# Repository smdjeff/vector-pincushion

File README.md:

# vector-pincushion

## Allows CRT swaps between various vector game boards and deflection boards. 

Finding tubes for vector arcade displays is difficult and being able to mix and match deflection boards, TV CRTs and arcade PCBs is becoming a necessity. Some arcade games relied on an exact combination of tube shape, yoke, and game board to correctly display.  There may be analog corrections on either the arcade PCB or the deflection board or even the CRT yoke and neck. The Amplifone deflection boards contain no corrections, so when used with a Wells Gardner game PCB adding a correction board is a necessity to add the missing circuity. Tempest PCBs lacked the adjustments as did Sega vectors, but more advanced games like Major Havoc and Star Wars had them on the game boards rather than the deflection boards.

This board allows correction or decorrection as required depending on what you have combined.

### Linearity adjustment 
applies the function _X = X * k_ and _Y = Y * k_ allowing calibration of straightness in diagonally drawn vectors. When set to expansion mode, the correction will cause lines to be drawn further and further outward from the center. When set to shrink mode, the correction will cause lines to be drawn closer and closer the further they are from the center.

### Pincushion correction 
applies the function _X = X * k * Y_ and _Y = Y * k * X_ allowing for each axis to be drawn further or closer toward the center depending on the *opposite* axis distance from center.

## Features

* Barreling correction mode
* Pincushion correction mode
* Linearity shrinking mode
* Linearity expansion mode
* Performs geometric distortion math in analog circuity
* Single 5V supply
* No unobtanium voltage dependent resistor required
* No unobtanium MC1495 analog multipler required
* All new design around the AD633 analog multipler typically used in very high end audio equipment.
* Supports 2x faster speed than orignal when used with TI-H 5.25MHz bandwidth amplifiers.

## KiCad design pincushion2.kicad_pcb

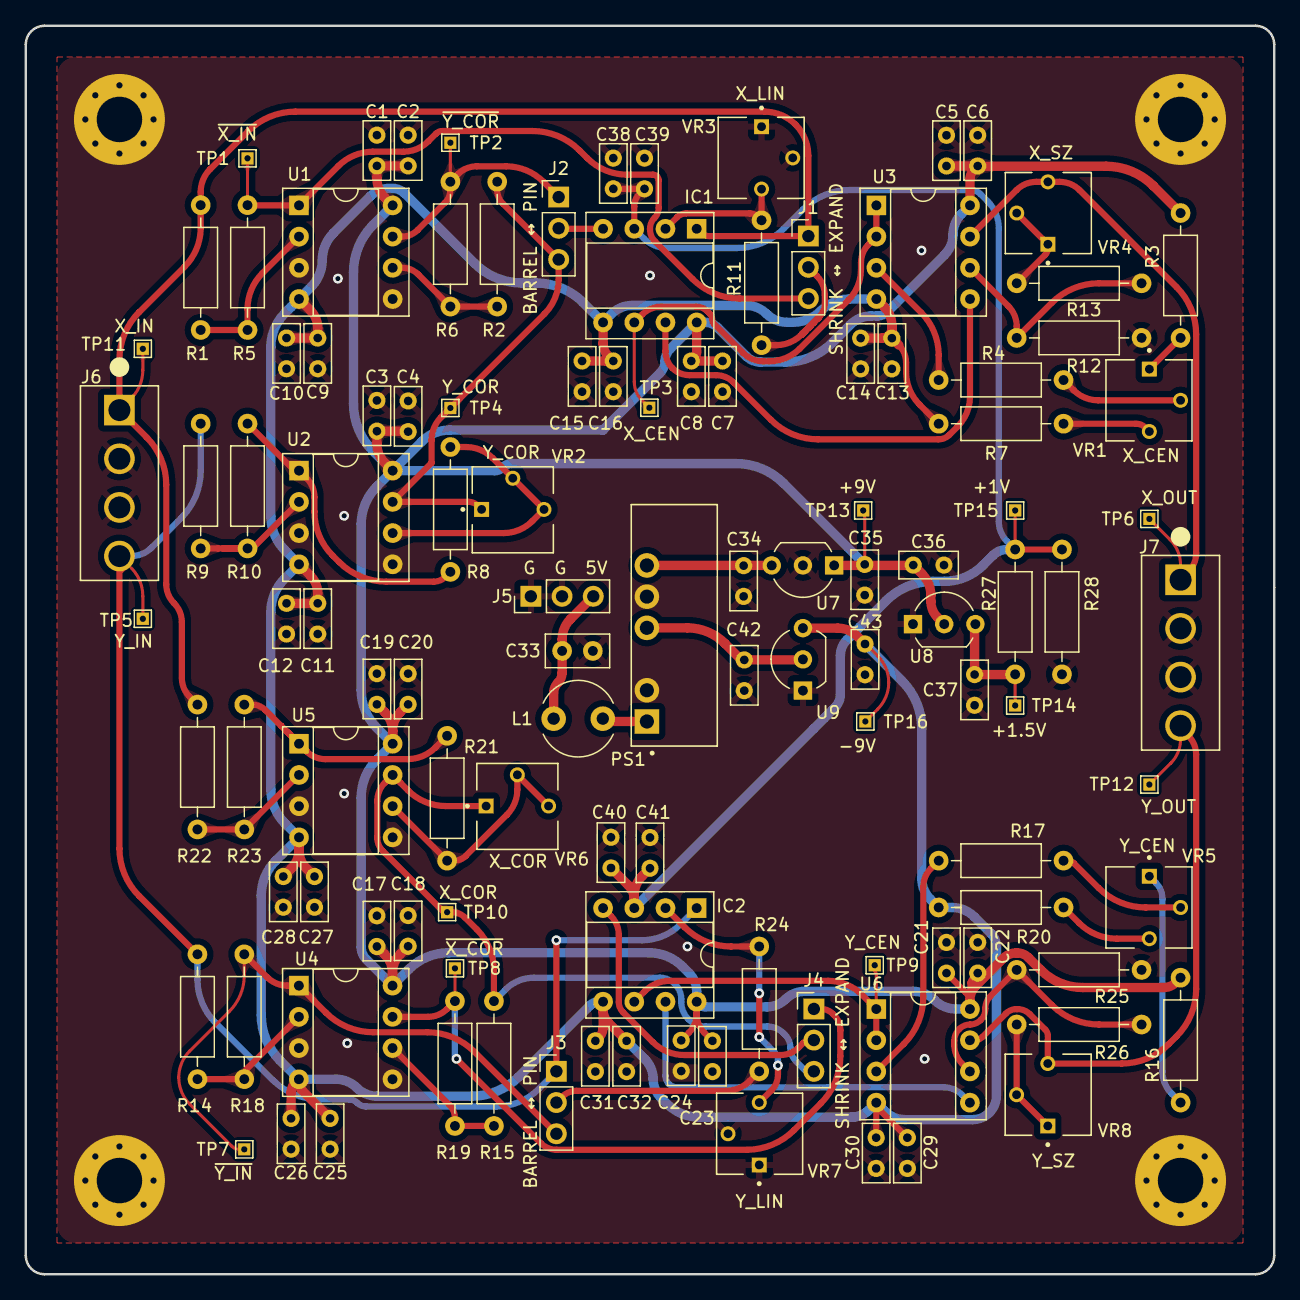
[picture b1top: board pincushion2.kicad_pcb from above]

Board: 2 copper layers, 101.6 x 101.6 mm, 119 parts (0 on the bottom side), 51 nets.

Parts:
C1, C3, C5, C7, C9, C11, C13, C15, C17, C19, C21, C23, C25, C27, C29, C31, C35, C39, C41, C43: .1uF; C_Rect_L4.6mm_W2.0mm_P2.50mm_MKS02_FKP02
C2, C4, C6, C8, C10, C12, C14, C16, C18, C20, C22, C24, C26, C28, C30, C32, C38, C40: .01uF; C_Rect_L4.6mm_W2.0mm_P2.50mm_MKS02_FKP02
C33: 10uF CER; C_Disc_D5.0mm_W2.5mm_P2.50mm
C34, C42: .33uF; C_Rect_L4.6mm_W2.0mm_P2.50mm_MKS02_FKP02
C36, C37: 1uF; C_Rect_L4.6mm_W2.0mm_P2.50mm_MKS02_FKP02
H1, H2, H3, H4: MountingHole_Pad; MountingHole_3.7mm_Pad_Via
IC1, IC2: AD633JN; DIP-8_W7.62mm_Socket
J1, J2, J3, J4, J5: Conn_01x03_Male; PinHeader_1x03_P2.54mm_Vertical
J6, J7: 640385-4; TE_640385-4
L1: 22uH; L_Radial_D6.0mm_P4.00mm
PS1: RD-0512D; CONV_RD-0512D
R1, R2, R4, R5, R6, R9, R14, R15, R17, R18, R19, R22, R28: 100k; R_Axial_DIN0207_L6.3mm_D2.5mm_P10.16mm_Horizontal
R3, R7, R16, R20: 1M; R_Axial_DIN0207_L6.3mm_D2.5mm_P10.16mm_Horizontal
R8, R10, R12, R21, R23, R25: 10k; R_Axial_DIN0207_L6.3mm_D2.5mm_P10.16mm_Horizontal
R11, R24, R27: 50k; R_Axial_DIN0207_L6.3mm_D2.5mm_P10.16mm_Horizontal
R13, R26: 70k; R_Axial_DIN0207_L6.3mm_D2.5mm_P10.16mm_Horizontal
TP1, TP2, TP3, TP4, TP5, TP6, TP7, TP8, TP9, TP10, TP11, TP12, TP13, TP14, TP15, TP16: TestPoint; TestPoint_THTPad_1.0x1.0mm_Drill0.5mm
U1, U2, U3, U4, U5, U6: TL082; DIP-8_W7.62mm_Socket
U7: DI78L09ZAB; TO-92_Inline_Wide
U8: MCP1702-1502E/TO; TO-92_Inline_Wide
U9: DI79L09ZAB; TO-92_Inline_Wide
VR1, VR5: 100k; TRIM_3362P-1-103LF
VR2, VR6: 10k; TRIM_3362P-1-103LF
VR3, VR4, VR7, VR8: 20k; TRIM_3362P-1-103LF

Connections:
+1V: C38.1, C39.1, C40.1, C41.1, IC1.3 (Y1), IC2.3 (Y1), R27.1, R28.2, TP15.1
+1V5: C37.1, R27.2, TP14.1, U8.3 (VO)
+5V: C33.1, J5.3, L1.1
+9V: C1.1, C2.1, C3.1, C4.1, C5.1, C6.1, C7.1, C8.1, C17.1, C18.1, C19.1, C20.1, C21.1, C22.1, C23.1, C24.1, C35.1, C36.1, IC1.8 (+VS), IC2.8 (+VS), R3.2, R16.2, TP13.1, U1.8 (V+), U2.8 (V+), U3.8 (V+), U4.8 (V+), U5.8 (V+), U6.8 (V+), U7.1 (VO), U8.2 (VI)
+12V: C34.1, PS1.6 (+VOUT), U7.3 (VI)
-9V: C9.2, C10.2, C11.2, C12.2, C13.2, C14.2, C15.2, C16.2, C25.2, C26.2, C27.2, C28.2, C29.2, C30.2, C31.2, C32.2, C43.1, IC1.5 (-VS), IC2.5 (-VS), R7.1, R20.1, TP16.1, U1.4 (V-), U2.4 (V-), U3.4 (V-), U4.4 (V-), U5.4 (V-), U6.4 (V-), U9.3 (VO)
-12V: C42.1, PS1.4 (-VOUT), U9.2 (VI)
/amps-x/X_CEN: IC1.6 (Z), TP3.1, U3.1, U3.2 (-)
/amps-x/X_LIN: IC1.2 (X2), R11.1, VR3.3
/amps-x/Y_COR: J2.3, R2.1, TP4.1, U2.7, VR2.1
/amps-x/~X_IN: J1.3, R5.2, TP1.1, U1.1
/amps-x/~Y_COR: J2.1, R6.2, TP2.1, U1.7
/amps-y/X_COR: J4.3, R15.1, TP10.1, U5.7, VR6.1
/amps-y/Y_CEN: IC2.6 (Z), TP9.1, U6.1, U6.2 (-)
/amps-y/Y_LIN: IC2.2 (X2), R24.1, VR7.3
/amps-y/~X_COR: J4.1, R19.2, TP8.1, U4.7
/amps-y/~Y_IN: J3.3, R18.2, TP7.1, U4.1
GND: C1.2, C2.2, C3.2, C4.2, C5.2, C6.2, C7.2, C8.2, C9.1, C10.1, C11.1, C12.1, C13.1, C14.1, C15.1, C16.1, C17.2, C18.2, C19.2, C20.2, C21.2, C22.2, C23.2, C24.2, C25.1, C26.1, C27.1, C28.1, C29.1, C30.1, C31.1, C32.1, C33.2, C34.2, C35.2, C36.2, C37.2, C38.2, C39.2, C40.2, C41.2, C42.2, C43.2, H1.1, H2.1, H3.1, H4.1, J5.1, J5.2, J6.2, J6.3, J7.2, J7.3, PS1.2 (-VIN), PS1.5 (COM), R12.1, R25.1, R28.1, U1.3 (+), U1.5 (+), U2.3 (+), U2.5 (+), U4.3 (+), U4.5 (+), U5.3 (+), U5.5 (+), U7.2 (GND), U8.1 (GND), U9.1 (GND), VR3.1, VR3.2, VR7.1, VR7.2
unnamed: IC1.7 (W), U3.5 (+)
unnamed: IC1.4 (Y2), J2.2
unnamed: IC2.7 (W), U6.5 (+)
unnamed: IC2.4 (Y2), J4.2
unnamed: J1.2, R11.2
unnamed: J3.2, R24.2
unnamed: L1.2, PS1.1 (+VIN)
unnamed: R3.1, VR1.1
unnamed: R4.1, VR1.2
unnamed: R7.2, VR1.3
unnamed: R8.1, R10.2, U2.1
unnamed: R13.2, VR4.1, VR4.2
unnamed: R16.1, VR5.1
unnamed: R17.1, VR5.2
unnamed: R20.2, VR5.3
unnamed: R21.1, R23.2, U5.1
unnamed: R26.2, VR8.1, VR8.2
unnamed: R1.2, R5.1, U1.2 (-)
unnamed: R2.2, R6.1, U1.6 (-)
unnamed: R9.2, R10.1, U2.2 (-)
unnamed: R8.2, U2.6 (-), VR2.2, VR2.3
unnamed: R4.2, U3.3 (+)
unnamed: R12.2, R13.1, U3.6 (-)
unnamed: R14.2, R18.1, U4.2 (-)
unnamed: R15.2, R19.1, U4.6 (-)
unnamed: R22.2, R23.1, U5.2 (-)
unnamed: R21.2, U5.6 (-), VR6.2, VR6.3
unnamed: R17.2, U6.3 (+)
unnamed: R25.2, R26.1, U6.6 (-)
X_IN: IC1.1 (X1), J1.1, J6.1, R1.1, R22.1, TP11.1
X_OUT: J7.1, TP6.1, U3.7, VR4.3
Y_IN: IC2.1 (X1), J3.1, J6.4, R9.1, R14.1, TP5.1
Y_OUT: J7.4, TP12.1, U6.7, VR8.3

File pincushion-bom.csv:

Qty,Reference(s),Value,Part Number
20,"C1, C3, C5, C7, C9, C11, C13, C15, C17, C19, C21, C23, C25, C27, C29, C31, C35, C39, C41, C43",.1uF,K104K15X7RF5TL2
18,"C2, C4, C6, C8, C10, C12, C14, C16, C18, C20, C22, C24, C26, C28, C30, C32, C38, C40",.01uF,K103K10X7RF53L2
1,C33,10uF CER, FG16X7R1E106KRT06
2,"C34, C42",.33uF,FA24X7R1H334KNU06
2,"C36, C37",1uF,FG28X7R1E105KRT00
2,"IC1, IC2",AD633JN,AD633JN
5,"J1, J2, J3, J4, J5",Conn_01x03_Male,DNP
2,"J6, J7",640385-4,WM50027-04-ND
1,L1,22uH,11R223C
1,PS1,RD-0512D,RD-0512D
1,"R28",100k 0.1%,RN55E1003BRE6
12,"R1, R2, R4, R5, R6, R9, R14, R15, R17, R18, R19, R22",100k 1%,MFR-25FRF52-100K
4,"R3, R7, R16, R20",1M,MF0207FRE52-1M
6,"R8, R10, R12, R21, R23, R25",10k,MFR-25FRF52-10K
3,"R11, R24, R27",50k 0.1%,RN55C5002BB14
2,"R13, R26",70k,RN55D7002FB14
6,"U1, U2, U3, U4, U5, U6",TL082,TL082CP
1,U7,DI78L09ZAB,DI78L09ZAB
1,U8,MCP1702-1502E/TO,MCP1702-1502E/TO
1,U9,DI79L09ZAB,DI79L09ZAB
2,"VR1, VR5",100k,3362P-1-104LF
2,"VR2, VR6",10k,3362P-1-103LF
4,"VR3, VR4, VR7, VR8",20k,3362P-1-203LF

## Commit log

2024-07-03 Create docs
2024-07-03 no message
2024-07-04 correct silkscreen
2024-07-04 move input connector so board can stack with the sega-amplifone board
2024-07-05 add bom
2024-07-07 add thermals to caps and resistors. more pitch spacing for inductor and TO92 packages.

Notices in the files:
pincushion2.kicad_pcb:
TRANSLATOR (C)2024
